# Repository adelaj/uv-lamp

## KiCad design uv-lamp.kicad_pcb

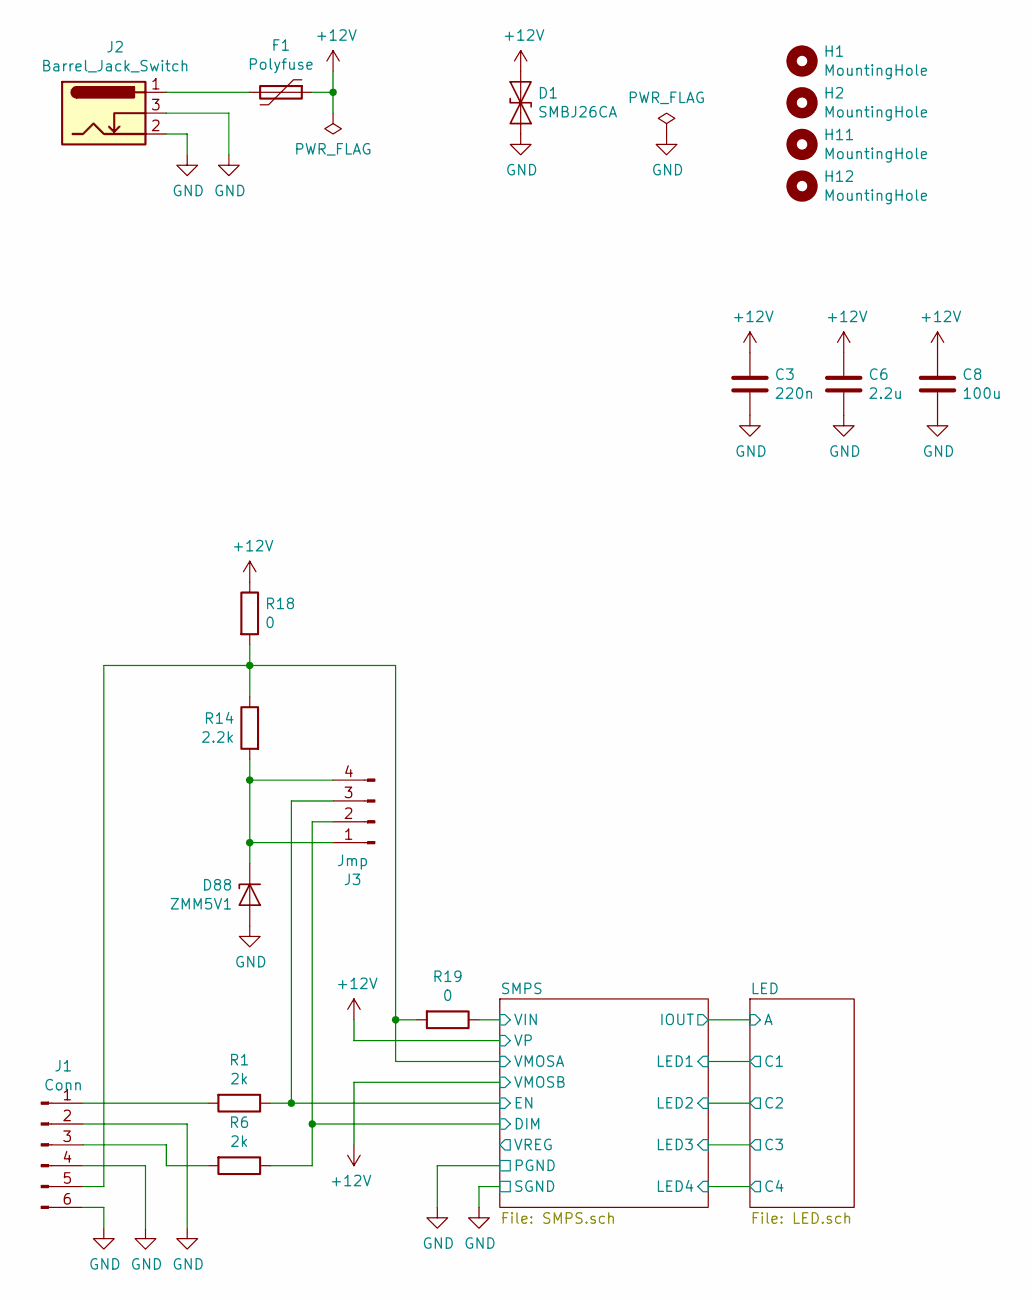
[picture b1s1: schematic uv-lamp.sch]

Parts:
C3: 220n; C_1206_HandSoldering
C6: 2.2u; C_1210_HandSoldering
C8: 100u; C_1812_HandSoldering
D1: SMBJ26CA; D_SMB_Handsoldering
D88: ZMM5V1; D_MiniMELF_Handsoldering
F1: Polyfuse; C_Rect_L7.0mm_W2.5mm_P5.00mm
H1, H2, H11, H12: MountingHole; MountingHole_4.3mm_M4_Pad
J1: Conn; Pin_Header_Straight_2x03_Pitch2.54mm
J2: Barrel_Jack_Switch; BARREL_JACK
J3: Jmp; Pin_Header_Straight_2x02_Pitch2.54mm
R1, R6: 2k; R_1206_HandSoldering
R14: 2.2k; R_1206_HandSoldering
R18, R19: 0; R_2010_HandSoldering

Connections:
+12V: C3.1, C6.1, C8.1, D1.1 (A1), F1.1, R18.1; also elsewhere on the board
/SMPS/DIM: J3.2, R6.1; also elsewhere on the board
/SMPS/EN: J3.3, R1.1; also elsewhere on the board
/SMPS/VIN: R19.1; also elsewhere on the board
/SMPS/VMOSA: J1.5, R14.1, R18.2, R19.2; also elsewhere on the board
GND: C3.2, C6.2, C8.2, D1.2 (A2), D88.2 (A), J1.2, J1.4, J1.6, J2.2, J2.3; also elsewhere on the board
unnamed: D88.1 (K), J3.1, J3.4, R14.2
unnamed: F1.2, J2.1
unnamed: J1.1, R1.2
unnamed: J1.3, R6.2

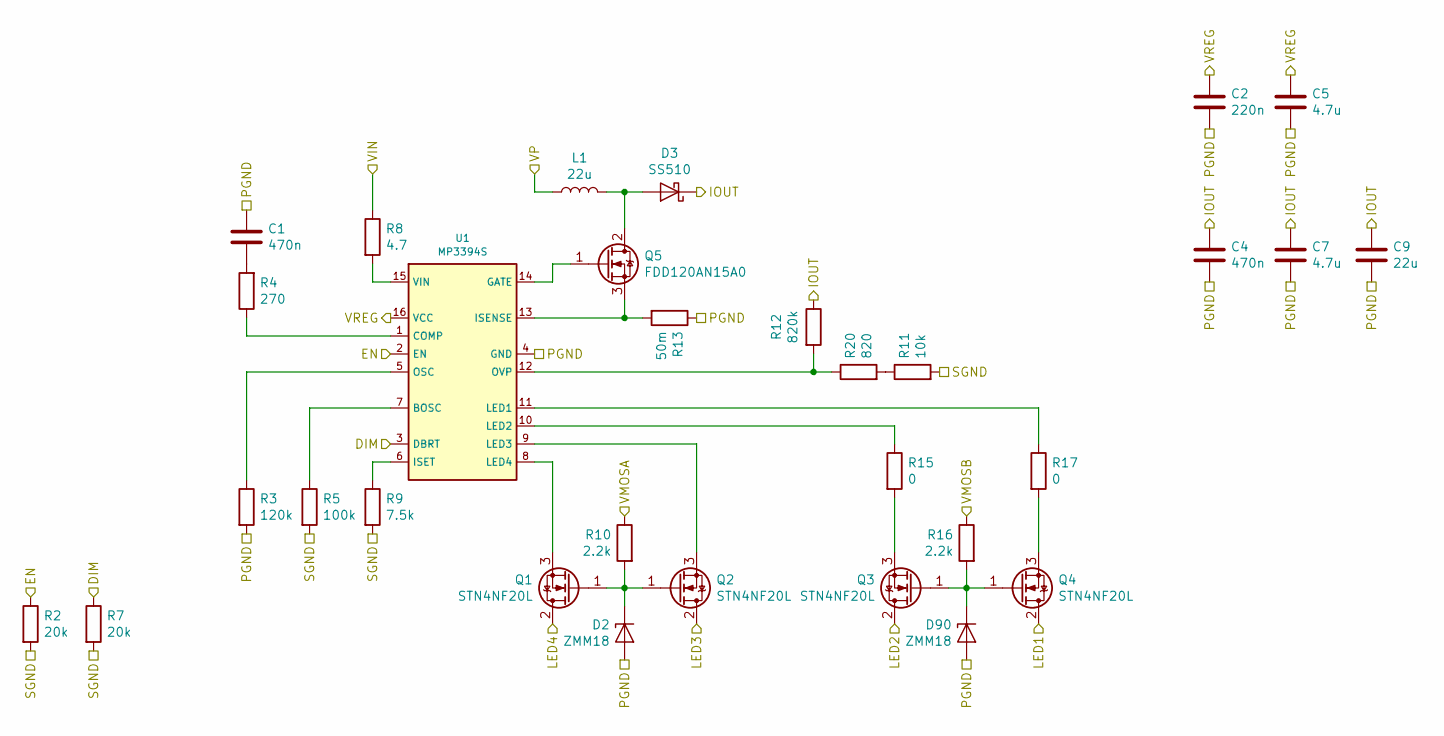
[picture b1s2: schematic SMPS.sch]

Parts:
C1: 470n; C_1206_HandSoldering
C2: 220n; C_1206_HandSoldering
C4: 470n; C_1812_HandSoldering
C5: 4.7u; C_1210_HandSoldering
C7: 4.7u; C_1812_HandSoldering
C9: 22u; C_1812_HandSoldering
D2, D90: ZMM18; D_MiniMELF_Handsoldering
D3: SS510; D_SMC_Handsoldering
L1: 22u; L_12x12mm_h8mm
Q1, Q2, Q3, Q4: STN4NF20L; SOT-223-3_TabPin2
Q5: FDD120AN15A0; TO-252-2
R2, R7: 20k; R_1206_HandSoldering
R3: 120k; R_1206_HandSoldering
R4: 270; R_1206_HandSoldering
R5: 100k; R_1206_HandSoldering
R8: 4.7; R_1206_HandSoldering
R9: 7.5k; R_1206_HandSoldering
R10, R16: 2.2k; R_1206_HandSoldering
R11: 10k; R_1206_HandSoldering
R12: 820k; R_1206_HandSoldering
R13: 50m; R_2512_HandSoldering
R15, R17: 0; R_2010_HandSoldering
R20: 820; R_1206_HandSoldering
U1: MP3394S; SOIC-16_3.9x9.9mm_Pitch1.27mm

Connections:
+12V: L1.1, R16.1; also elsewhere on the board
/LED/A: C4.1, C7.1, C9.1, D3.1 (K), R12.1; also elsewhere on the board
/LED/C1: Q4.2 (D); also elsewhere on the board
/LED/C2: Q3.2 (D); also elsewhere on the board
/LED/C3: Q2.2 (D); also elsewhere on the board
/LED/C4: Q1.2 (D); also elsewhere on the board
/SMPS/DIM: R7.1, U1.3 (DBRT); also elsewhere on the board
/SMPS/EN: R2.1, U1.2 (EN); also elsewhere on the board
/SMPS/VIN: R8.1; also elsewhere on the board
/SMPS/VMOSA: R10.1; also elsewhere on the board
/SMPS/VREG: C2.1, C5.2, U1.16 (VCC)
GND: C1.2, C2.2, C4.2, C5.1, C7.2, C9.2, D2.2 (A), D90.2 (A), R2.2, R3.2, R5.2, R7.2, R9.2, R11.2, R13.1, U1.4 (GND); also elsewhere on the board
unnamed: C1.1, R4.2
unnamed: D2.1 (K), Q1.1 (G), Q2.1 (G), R10.2
unnamed: D3.2 (A), L1.2, Q5.2 (D)
unnamed: D90.1 (K), Q3.1 (G), Q4.1 (G), R16.2
unnamed: Q1.3 (S), U1.8 (LED4)
unnamed: Q2.3 (S), U1.9 (LED3)
unnamed: Q3.3 (S), R15.2
unnamed: Q4.3 (S), R17.2
unnamed: Q5.1 (G), U1.14 (GATE)
unnamed: Q5.3 (S), R13.2, U1.13 (ISENSE)
unnamed: R3.1, U1.5 (OSC)
unnamed: R4.1, U1.1 (COMP)
unnamed: R5.1, U1.7 (BOSC)
unnamed: R8.2, U1.15 (VIN)
unnamed: R9.1, U1.6 (ISET)
unnamed: R11.1, R20.2
unnamed: R12.2, R20.1, U1.12 (OVP)
unnamed: R15.1, U1.10 (LED2)
unnamed: R17.1, U1.11 (LED1)

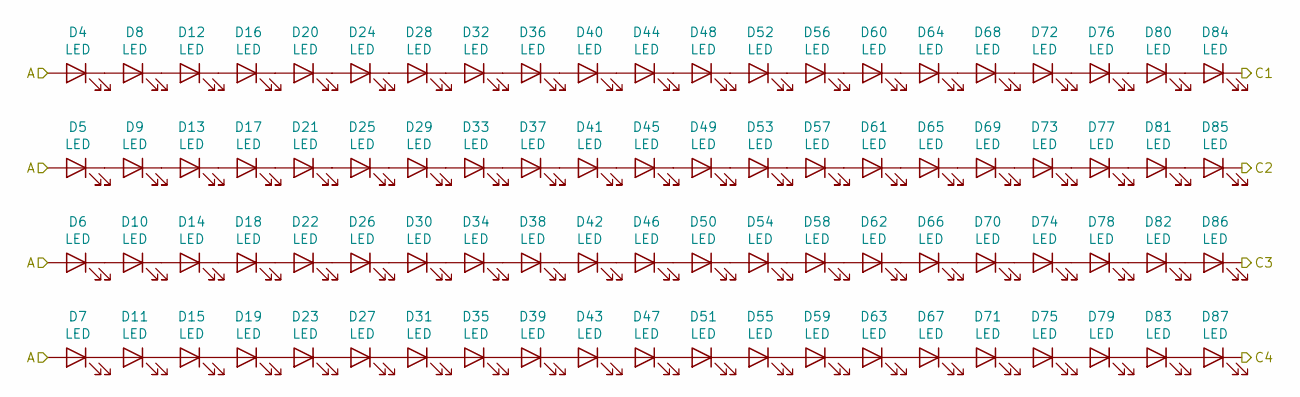
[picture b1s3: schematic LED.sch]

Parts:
D4, D5, D6, D7, D8, D9, D10, D11, D12, D13, D14, D15, D16, D17, D18, D19, D20, D21, D22, D23, D24, D25, D26, D27, D28, D29, D30, D31, D32, D33, D34, D35, D36, D37, D38, D39, D40, D41, D42, D43, D44, D45, D46, D47, D48, D49, D50, D51, D52, D53, D54, D55, D56, D57, D58, D59, D60, D61, D62, D63, D64, D65, D66, D67, D68, D69, D70, D71, D72, D73, D74, D75, D76, D77, D78, D79, D80, D81, D82, D83, D84, D85, D86, D87: LED; D_LED_5730

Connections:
/LED/A: D4.2 (A), D5.2 (A), D6.2 (A), D7.2 (A); also elsewhere on the board
/LED/C1: D84.1 (K); also elsewhere on the board
/LED/C2: D85.1 (K); also elsewhere on the board
/LED/C3: D86.1 (K); also elsewhere on the board
/LED/C4: D87.1 (K); also elsewhere on the board
unnamed: D4.1 (K), D8.2 (A)
unnamed: D5.1 (K), D9.2 (A)
unnamed: D10.1 (K), D14.2 (A)
unnamed: D6.1 (K), D10.2 (A)
unnamed: D11.1 (K), D15.2 (A)
unnamed: D7.1 (K), D11.2 (A)
unnamed: D12.1 (K), D16.2 (A)
unnamed: D8.1 (K), D12.2 (A)
unnamed: D13.1 (K), D17.2 (A)
unnamed: D9.1 (K), D13.2 (A)
unnamed: D14.1 (K), D18.2 (A)
unnamed: D15.1 (K), D19.2 (A)
unnamed: D16.1 (K), D20.2 (A)
unnamed: D17.1 (K), D21.2 (A)
unnamed: D18.1 (K), D22.2 (A)
unnamed: D19.1 (K), D23.2 (A)
unnamed: D20.1 (K), D24.2 (A)
unnamed: D21.1 (K), D25.2 (A)
unnamed: D22.1 (K), D26.2 (A)
unnamed: D23.1 (K), D27.2 (A)
unnamed: D24.1 (K), D28.2 (A)
unnamed: D25.1 (K), D29.2 (A)
unnamed: D26.1 (K), D30.2 (A)
unnamed: D27.1 (K), D31.2 (A)
unnamed: D28.1 (K), D32.2 (A)
unnamed: D29.1 (K), D33.2 (A)
unnamed: D30.1 (K), D34.2 (A)
unnamed: D31.1 (K), D35.2 (A)
unnamed: D32.1 (K), D36.2 (A)
unnamed: D33.1 (K), D37.2 (A)
unnamed: D34.1 (K), D38.2 (A)
unnamed: D35.1 (K), D39.2 (A)
unnamed: D36.1 (K), D40.2 (A)
unnamed: D37.1 (K), D41.2 (A)
unnamed: D38.1 (K), D42.2 (A)
unnamed: D39.1 (K), D43.2 (A)
unnamed: D40.1 (K), D44.2 (A)
unnamed: D41.1 (K), D45.2 (A)
unnamed: D42.1 (K), D46.2 (A)
unnamed: D43.1 (K), D47.2 (A)
unnamed: D44.1 (K), D48.2 (A)
unnamed: D45.1 (K), D49.2 (A)
unnamed: D46.1 (K), D50.2 (A)
unnamed: D47.1 (K), D51.2 (A)
unnamed: D48.1 (K), D52.2 (A)
unnamed: D49.1 (K), D53.2 (A)
unnamed: D50.1 (K), D54.2 (A)
unnamed: D51.1 (K), D55.2 (A)
unnamed: D52.1 (K), D56.2 (A)
unnamed: D53.1 (K), D57.2 (A)
unnamed: D54.1 (K), D58.2 (A)
unnamed: D55.1 (K), D59.2 (A)
unnamed: D56.1 (K), D60.2 (A)
unnamed: D57.1 (K), D61.2 (A)
unnamed: D58.1 (K), D62.2 (A)
unnamed: D59.1 (K), D63.2 (A)
unnamed: D60.1 (K), D64.2 (A)
unnamed: D61.1 (K), D65.2 (A)
unnamed: D62.1 (K), D66.2 (A)
unnamed: D63.1 (K), D67.2 (A)
unnamed: D64.1 (K), D68.2 (A)
unnamed: D65.1 (K), D69.2 (A)
unnamed: D66.1 (K), D70.2 (A)
unnamed: D67.1 (K), D71.2 (A)
unnamed: D68.1 (K), D72.2 (A)
unnamed: D69.1 (K), D73.2 (A)
unnamed: D70.1 (K), D74.2 (A)
unnamed: D71.1 (K), D75.2 (A)
unnamed: D72.1 (K), D76.2 (A)
unnamed: D73.1 (K), D77.2 (A)
unnamed: D74.1 (K), D78.2 (A)
unnamed: D75.1 (K), D79.2 (A)
unnamed: D76.1 (K), D80.2 (A)
unnamed: D77.1 (K), D81.2 (A)
unnamed: D78.1 (K), D82.2 (A)
unnamed: D79.1 (K), D83.2 (A)
unnamed: D80.1 (K), D84.2 (A)
unnamed: D81.1 (K), D85.2 (A)
unnamed: D82.1 (K), D86.2 (A)
unnamed: D83.1 (K), D87.2 (A)

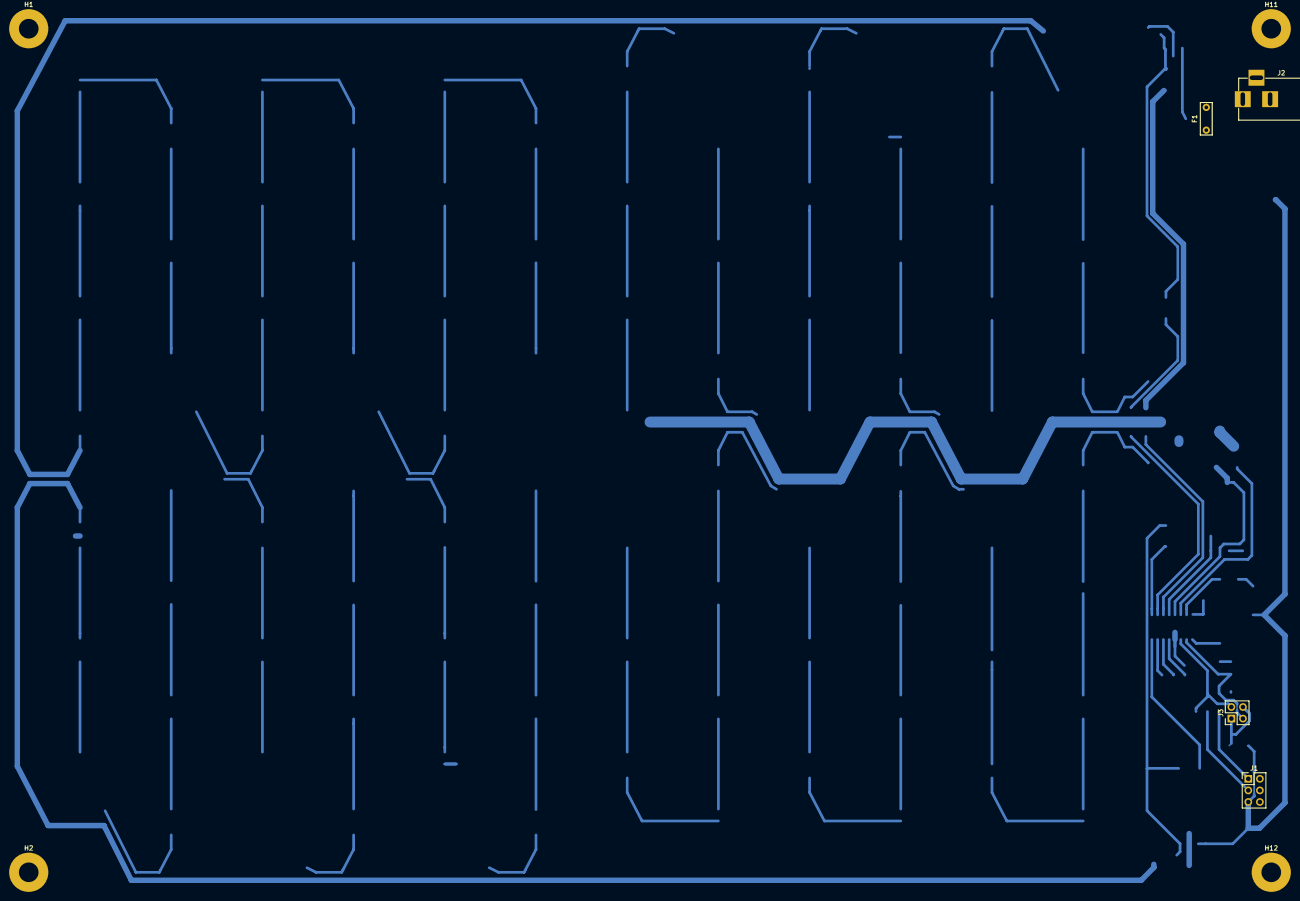
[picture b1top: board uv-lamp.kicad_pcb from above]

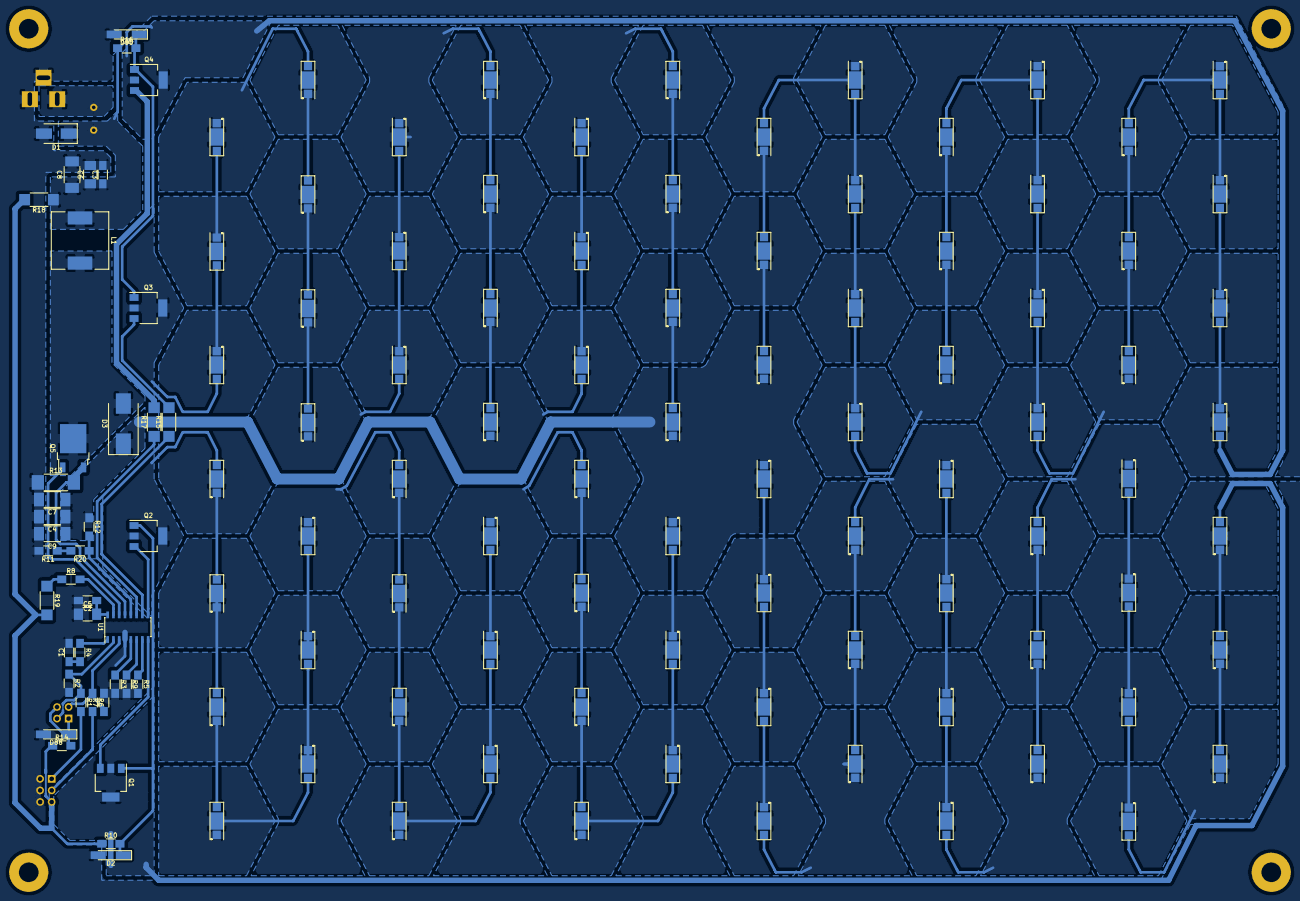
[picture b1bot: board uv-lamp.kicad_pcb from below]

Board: 2 copper layers, 133 parts (125 on the bottom side), 115 nets.
